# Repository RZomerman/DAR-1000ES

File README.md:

# Sony DAR-1000ES Conversion Project

This repository contains the project documentation converted from the original Word document into chapter-based GitHub Flavored Markdown.

## Chapters

For current AHCT wiring, brightness calculations and radio operation, start
with the [screen-driver operating guide](13-screen-driver-operating-guide.md).
Shared STB on **both** TD chips corrected the earlier multiplexing corruption;
clean 22-matrix text and scrolling were observed. Firmware 0.3.28 includes
internet radio, explicitly authorized full-width NOW PLAYING, and source
channel/bitrate/playback/genre indicators.
Installed 0.3.29 adds selectable Option 1 stereo spectrum (11 real PCM frequency
bands per channel), verified with isolated TD-model captures and decoded
stereo/mono/silence fixtures; the user confirmed the bars at 0.75% brightness.
Version 0.3.30 adds MONO 1/2 bank labels while retaining actual-source STEREO
and fixes measured scan gaps with longer DMA batching. A connected camera
snapshot confirms all 22 bars and STEREO/MONO 1/MONO 2/TUNED at 0.75%
per-grid duty. User confirmation of residual flicker is still pending;
a still image cannot establish temporal stability.
Physical voltage/current validation remains outstanding.
Firmware 0.3.31 boots with the fixed AHCT v2 GPIO map. Display output still
starts stopped; the legacy profile remains an isolated-only runtime option.
Installed firmware 0.3.32 adds eight display modes and shared short-/long-press
controls for a future Display Mode button, with 0.25% / 0.5% / 0.75% DIM cycling.
All eight modes and DIM cycling were checked on the isolated ESP; after
reconnection, Equalizer was restored at 0.75% per-grid duty.

For current display control, start with the
[fixed-element guide](08-esp-display-driver-specification.md#6-fixed-element-control-guide)
and [generic 5x7 matrix guide](08-esp-display-driver-specification.md#7-generic-5x7-matrix-guide).
The [annotated reference comparison](media/display-reference-coverage.svg)
matches every functional symbol in the FL701 drawing to an observed command.
Element mapping is complete at that level. Clean full-screen multiplexing
has now been observed with shared STB; electrical validation remains outstanding.

The [complete display bitmap catalogue](10-display-bitmap-catalogue.md)
includes 5x7 pixel patterns and HEX values for uppercase/lowercase letters,
digits, punctuation, a music note and seven level bars.

1. [DAR-1000ES Conversion](01-conversion.md)
2. [DAR-1000ES Display Control](02-display-control.md)
3. [DAR-1000ES Sound Path](03-sound-path.md)
4. [DAR-1000ES Program and Keypad Baseline](04-program-and-keypad-baseline.md)
5. [Bus Capture Findings and Key Reports](05-bus-capture-findings.md)
6. [Direct Display driving](06-direct-display-driving.md)
7. [Audio Control Findings and Next-Step Plan](07-audio-control-findings-and-plan.md)
8. [ESP32 Display-Driver Specification](08-esp-display-driver-specification.md)
9. [Music Note Bitmap](09-music-note-bitmap.md)
10. [Display Bitmap Catalogue](10-display-bitmap-catalogue.md)
11. [Live ESP32 Display Driver and Validation](11-live-display-driver-and-validation.md)
12. [TD62C950RF Timing Revalidation](12-td62c950rf-timing-revalidation.md)
13. [Screen Driver Operating Guide](13-screen-driver-operating-guide.md)
14. [Keypad Mapping](14-keypad-mapping.md)
15. [Split-setup Architecture and Travel Demo](15-split-setup-architecture.md)

Proposed behavior: [Chapter 18: Startup Procedure](18-startup-procedure.md)
specifies the snow/title sequence, saved station/brightness/display recovery and the
verification needed before automatic hardware-ready authorization can replace
manual confirmation. It is not implemented startup behavior.

Images used by the chapters are stored in [`media/`](media/).

The [ESP32 firmware](firmware/README-DAR-1000ES.md) includes internet radio,
the opt-in display timing/NOW PLAYING profile and the preserved upstream license.

## Control Integration Options

1. **Reuse the original controls (partially characterized):** Investigate the parallel bus between the system controller and display/front-panel controller IC701 before bypassing the original control firmware. See the [internal bus protocol specification](SONY_DAR1000ES_Protocol_Spec.md) and [2026-11-02 capture findings](05-bus-capture-findings.md). Passive captures establish repeatable framing and key/display correlations, but masked bits, driver ownership and electrical assumptions still block reliable emulation.
2. **Direct display-driver control (optically mapped, driver experimental):** Captures at IC702/IC703 establish a 26-slot scan, 40 segment clocks and one grid clock per slot. Controlled one-hot tests now map all 770 matrix dots and all fixed functional elements shown in the reference. See the [operating guide](13-screen-driver-operating-guide.md), [element guide](08-esp-display-driver-specification.md) and [capture/validation history](06-direct-display-driving.md). Shared STB on both TD chips now gives clean full-width text and scrolling; electrical margins and current remain unverified. [DAR-1000ES Display Control](02-display-control.md) retains the original hardware proposal, not current wiring instructions.

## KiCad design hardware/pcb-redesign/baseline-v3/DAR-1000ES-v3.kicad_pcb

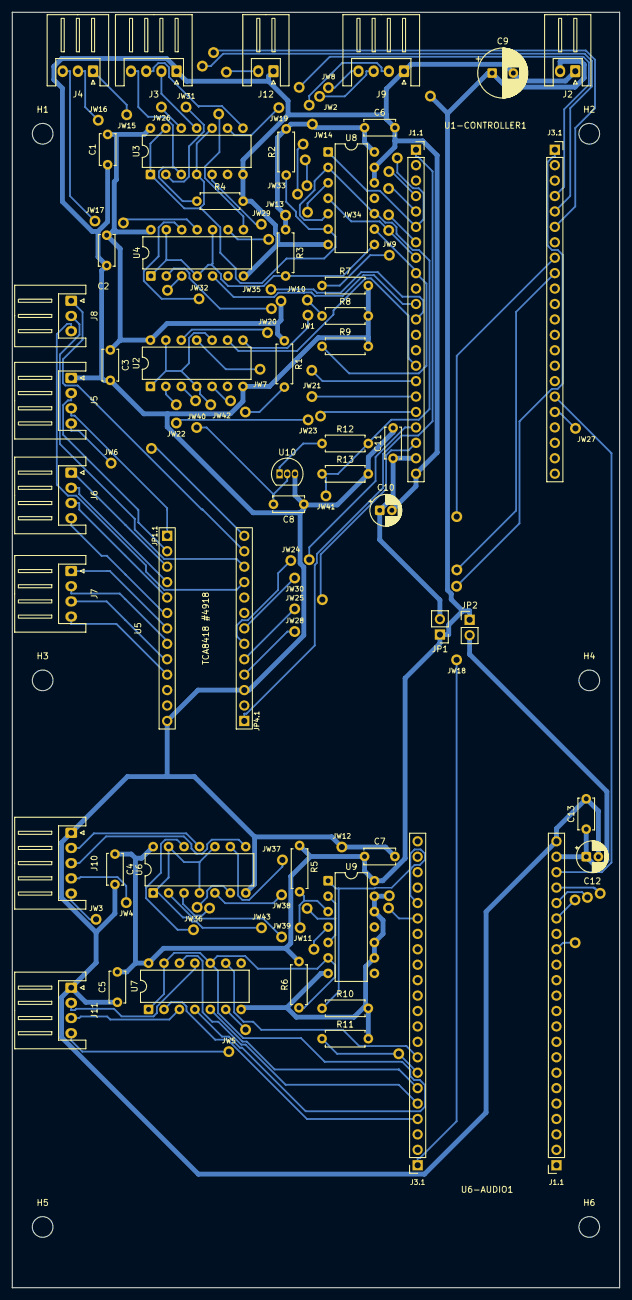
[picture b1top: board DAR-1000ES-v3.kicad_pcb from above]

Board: 2 copper layers, 100.0 x 210.0 mm, 99 parts (0 on the bottom side), 75 nets.

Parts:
C1, C2, C3, C4, C5: C; Bottom_Capacitor_THT__C_Disc_D5.0mm_W2.5mm_P5.00mm
C6, C7, C8, C11, C13: 100nF; Bottom_Capacitor_THT__C_Disc_D5.0mm_W2.5mm_P5.00mm
C9: 470uF 16V; Bottom_Capacitor_THT__CP_Radial_D8.0mm_P3.50mm
C10, C12: 100uF 16V; Bottom_Capacitor_THT__CP_Radial_D5.0mm_P2.00mm
H1, H2, H3, H4, H5, H6: M3_Clearance_3.4mm; MountingHole_3.4mm_M3_NPTH
J2: Conn_01x02; Bottom_Connector_JST__JST_XH_S2B-XH-A_1x02_P2.50mm_Horizont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
J3, J5, J6, J7, J9, J11: Conn_01x04; Bottom_Connector_JST__JST_XH_S4B-XH-A_1x04_P2.50mm_Horizont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
J4, J8: Conn_01x03; Bottom_Connector_JST__JST_XH_S3B-XH-A_1x03_P2.50mm_Horizont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
J10: DAC CONTROL; Bottom_Connector_JST__JST_XH_S5B-XH-A_1x05_P2.50mm_Horizont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
J12: SONY_5V_SENSE; Bottom_Connector_JST__JST_XH_S2B-XH-A_1x02_P2.50mm_Horizont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
JP1, JP2: Jumper_2_Bridged; Bottom_Connector_PinHeader_2.54mm__PinHeader_1x02_P2.54mm_V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
JW1: Insulated wire link; Bottom_InsulatedWire_JW1
JW2: Insulated wire link; Bottom_InsulatedWire_JW2
JW3: Insulated wire link; Bottom_InsulatedWire_JW3
JW4: Insulated wire link; Bottom_InsulatedWire_JW4
JW5: Insulated wire link; Bottom_InsulatedWire_JW5
JW6: Insulated wire link; Bottom_InsulatedWire_JW6
JW7: Insulated wire link; Bottom_InsulatedWire_JW7
JW8: Insulated wire link; Bottom_InsulatedWire_JW8
JW9: Insulated wire link; Bottom_InsulatedWire_JW9
JW10: Insulated wire link; Bottom_InsulatedWire_JW10
JW11: Insulated wire link; Bottom_InsulatedWire_JW11
JW12: Insulated wire link; Bottom_InsulatedWire_JW12
JW13: Insulated wire link; Bottom_InsulatedWire_JW13
JW14: Insulated wire link; Bottom_InsulatedWire_JW14
JW15: Insulated wire link; Bottom_InsulatedWire_JW15
JW16: Insulated wire link; Bottom_InsulatedWire_JW16
JW17: Insulated wire link; Bottom_InsulatedWire_JW17
JW18: Insulated wire link; Bottom_InsulatedWire_JW18
JW19: Insulated wire link; Bottom_InsulatedWire_JW19
JW20: Insulated wire link; Bottom_InsulatedWire_JW20
JW21: Insulated wire link; Bottom_InsulatedWire_JW21
JW22: Insulated wire link; Bottom_InsulatedWire_JW22
JW23: Insulated wire link; Bottom_InsulatedWire_JW23
JW24: Insulated wire link; Bottom_InsulatedWire_JW24
JW25: Insulated wire link; Bottom_InsulatedWire_JW25
JW26: Insulated wire link; Bottom_InsulatedWire_JW26
JW27: Insulated wire link; Bottom_InsulatedWire_JW27
JW28: Insulated wire link; Bottom_InsulatedWire_JW28
JW29: Insulated wire link; Bottom_InsulatedWire_JW29
JW30: Insulated wire link; Bottom_InsulatedWire_JW30
JW31: Insulated wire link; Bottom_InsulatedWire_JW31
JW32: Insulated wire link; Bottom_InsulatedWire_JW32
JW33: Insulated wire link; Bottom_InsulatedWire_JW33
JW34: Insulated wire link; Bottom_InsulatedWire_JW34
JW35: Insulated wire link; Bottom_InsulatedWire_JW35
JW36: Insulated wire link; Bottom_InsulatedWire_JW36
JW37: Insulated wire link; Bottom_InsulatedWire_JW37
JW38: Insulated wire link; Bottom_InsulatedWire_JW38
JW39: Insulated wire link; Bottom_InsulatedWire_JW39
JW40: Insulated wire link; Bottom_InsulatedWire_JW40
JW41: Insulated wire link; Bottom_InsulatedWire_JW41
JW42: Insulated wire link; Bottom_InsulatedWire_JW42
JW43: Insulated wire link; Bottom_InsulatedWire_JW43
R1, R2, R3, R4, R5, R6: 10k; Bottom_Resistor_THT__R_Axial_DIN0207_L6.3mm_D2.5mm_P7.62mm_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
R7, R8, R9, R10, R11, R13: 100k; Bottom_Resistor_THT__R_Axial_DIN0207_L6.3mm_D2.5mm_P7.62mm_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
R12: 1k; Bottom_Resistor_THT__R_Axial_DIN0207_L6.3mm_D2.5mm_P7.62mm_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
U1-CONTROLLER1, U6-AUDIO1: ESP32-S3-DevKitC-1-N16R8; Bottom_DAR1000ES__ESP32-S3-DevKitC-1_2xSocket_1x22_P2.54mm_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
U2, U3, U4, U6, U7: SN74AHCT125N; Bottom_Package_DIP__DIP-14_W7.62mm
U5: Adafruit_TCA8418_4918; Bottom_DAR1000ES__Adafruit_TCA8418_4918_2x13_P2.54mm_W12.70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
U8, U9: SN74AHCT00N; Bottom_Package_DIP__DIP-14_W7.62mm
U10: MCP100-475DI/TO; Bottom_Package_TO_SOT_THT__TO-92_Inline

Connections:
/A.MUTE: J9.2, JW1.1, U2.8
/ATT: J10.2, U6.11
/BCKI: J11.2, U7.11
/D.MUTE: J9.3, JW2.1, U2.3
/DATA: J11.3, U7.3
/FLCLEAR: J3.4, R4.1, U3.3
/FLGCLK: J3.3, U3.8
/FLGDATA: J3.2, U3.11
/IN0: J6.1, U5.JP1.3 (C0)
/IN1: J6.2, U5.JP1.4 (C1)
/IN2: J6.3, U5.JP1.5 (C2)
/IN3: J6.4, U5.JP1.6 (C3)
/IN4: J7.1, U5.JP1.7 (C4)
/IN5: J7.2, U5.JP1.8 (C5)
/IN6: J7.3, U5.JP1.9 (C6)
/IN7: J7.4, U5.JP1.10 (C7)
/INIT: J10.5, JW3.1, U6.3
/LATCH: J10.4, JW4.1, U6.6
/LRCK: J11.4, JW5.1, U7.6
/OUT0: J5.2, U5.JP1.2 (R0)
/OUT1: J5.3, U5.JP1.1 (R1)
/OUT2: J5.4, JW6.1, U5.JP4.13 (R2)
/OUT3: J8.1, U5.JP4.12 (R3)
/OUT4: J8.2, U5.JP4.11 (R4)
/OUT5: J8.3, U5.JP4.10 (R5)
/RELAY: J9.4, JW7.1, JW8.1, U2.11
/SHIFT: J10.3, U6.8
ENABLE_U2: JW9.1, R7.1, U1-CONTROLLER1.J1.6 (IO6), U8.1 (1A)
ENABLE_U3: JW10.1, R8.1, U1-CONTROLLER1.J1.8 (IO15), U8.4 (2A)
ENABLE_U4: R9.1, U1-CONTROLLER1.J1.9 (IO16), U8.9 (3A)
ENABLE_U6: R10.1, U6-AUDIO1.J3.18 (IO21), U9.1 (1A)
ENABLE_U7: JW11.1, R11.1, U6-AUDIO1.J3.7 (IO41), U9.4 (2A)
ESP_AUDIO_5V: C12.1, C13.1, JP2.2 (B), U6-AUDIO1.J1.21 (5V)
ESP_CTRL_5V: C10.1, C11.1, JP1.2 (B), U1-CONTROLLER1.J1.21 (5V)
GND: C1.1, C2.1, C3.2, C4.2, C5.1, C6.2, C7.2, C8.2, C9.2, C10.2, C11.2, C12.2, C13.2, J2.1, J3.1, J5.1, J9.1, J10.1, J11.1, J12.1, JW12.1, R4.2, R7.2, R8.2, R9.2, R10.2, R11.2, R13.2, U1-CONTROLLER1.J1.22 (GND), U2.7 (GND), U3.7 (GND), U4.7 (GND), U5.JP1.13 (GND), U5.JP4.3 (GND), U6.7 (GND), U6-AUDIO1.J1.22 (GND), U7.7 (GND), U8.7 (GND), U8.12 (4A), U8.13 (4B), U9.7 (GND), U9.9 (3A), U9.10 (3B), U9.12 (4A), U9.13 (4B), U10.3 (GND)
LOCAL_5V: C1.2, C2.2, C3.1, C4.1, C5.2, C6.1, C7.1, C9.1, J2.2, JP1.1 (A), JP2.1 (A), JW13.1, JW14.1, R1.1, R2.2, R3.1, R5.1, R6.2, U2.14 (VCC), U3.14 (VCC), U4.14 (VCC), U6.14 (VCC), U7.14 (VCC), U8.14 (VCC), U9.14 (VCC)
unnamed: J4.1, JW15.1, U4.8
unnamed: J4.2, JW16.1, U4.3
unnamed: J4.3, JW17.1, U4.11
unnamed: JW18.1, U1-CONTROLLER1.J3.1 (GND), U6-AUDIO1.J3.1 (GND)
unnamed: JW19.1, U1-CONTROLLER1.J3.4 (IO1), U3.9
unnamed: JW26.1, U1-CONTROLLER1.J3.5 (IO2), U3.12
unnamed: JW29.1, U1-CONTROLLER1.J1.4 (IO4), U3.5
unnamed: JW32.1, JW33.1, U1-CONTROLLER1.J1.5 (IO5), U4.12
unnamed: JW34.1, U1-CONTROLLER1.J1.7 (IO7), U4.9
unnamed: JW35.1, U1-CONTROLLER1.J1.12 (IO8), U4.2
unnamed: U1-CONTROLLER1.J1.15 (IO9), U2.9
unnamed: JW20.1, U1-CONTROLLER1.J1.16 (IO10), U2.12
unnamed: JW21.1, U1-CONTROLLER1.J1.17 (IO11), U2.5
unnamed: JW22.1, JW23.1, U1-CONTROLLER1.J1.18 (IO12), U2.2
unnamed: JW24.1, U1-CONTROLLER1.J1.19 (IO13), U5.JP4.6 (~INT)
unnamed: JW25.1, U1-CONTROLLER1.J1.20 (IO14), U5.JP4.5 (SDA)
unnamed: U1-CONTROLLER1.J1.11 (IO18), U4.5
unnamed: JW27.1, U1-CONTROLLER1.J3.18 (IO21), U6-AUDIO1.J1.19 (IO13)
unnamed: JW28.1, U1-CONTROLLER1.J3.9 (IO39), U5.JP4.4 (SCL)
unnamed: JW30.1, U1-CONTROLLER1.J3.8 (IO40), U5.JP4.7 (~RST)
unnamed: JW31.1, U1-CONTROLLER1.J3.6 (IO42), U3.2
unnamed: U1-CONTROLLER1.J3.17 (IO47), U6-AUDIO1.J1.20 (IO14)
unnamed: U1-CONTROLLER1.J1.1 (3V3), U5.JP4.1 (VIN)
unnamed: U6-AUDIO1.J3.4 (IO1), U7.2
unnamed: U6-AUDIO1.J3.5 (IO2), U7.12
unnamed: JW39.1, U6.2, U6-AUDIO1.J1.15 (IO9)
unnamed: JW36.1, U6.12, U6-AUDIO1.J1.17 (IO11)
unnamed: JW37.1, U6.9, U6-AUDIO1.J1.18 (IO12)
unnamed: U6-AUDIO1.J3.8 (IO40), U7.9
unnamed: U6-AUDIO1.J3.6 (IO42), U7.5
unnamed: JW38.1, U6.5, U6-AUDIO1.J3.17 (IO47)
SONY_5V_SENSE: C8.1, J12.2, JW40.1, U10.2 (VDD_SONY)
SONY_POWER_GOOD: JW41.1, R12.2, R13.1, U8.2 (1B), U8.5 (2B), U8.10 (3B), U9.2 (1B), U9.5 (2B)
SONY_RESET_N_RAW: R12.1, U10.1 (~RESET)
U2_OE_N: JW42.1, R1.2, U2.1, U2.4, U2.10, U2.13, U8.3 (1Y)
U3_OE_N: R2.1, U3.1, U3.4, U3.10, U3.13, U8.6 (2Y)
U4_OE_N: R3.2, U4.1, U4.4, U4.10, U4.13, U8.8 (3Y)
U6_OE_N: JW43.1, R5.2, U6.1, U6.4, U6.10, U6.13, U9.3 (1Y)
U7_OE_N: R6.1, U7.1, U7.4, U7.10, U7.13, U9.6 (2Y)

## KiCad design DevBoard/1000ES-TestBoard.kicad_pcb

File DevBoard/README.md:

# Sony DAR-1000ES ESP32 Development Board

## Overview

**Design proposal, not a hardware-validation report.** This document describes
the intended three-ESP development board, not the pinout of the current
display-test harness. The [current display-control guide](../08-esp-display-driver-specification.md)
records confirmed element mapping; it does not establish that this board's
audio, bus, keypad, power or isolation features have been validated.

This development board is designed as the primary hardware platform for the **Sony DAR-1000ES modernization project**. It enables rapid experimentation with multiple integration strategies while preserving the original Sony hardware wherever possible.

The board incorporates **three ESP32-S3 controllers**, although only two are expected to be required for the final solution. The third controller is included specifically as a contingency path for direct display control if communication through the original Sony system controller (IC701) proves impractical.

The objective of this board is to validate all critical hardware interfaces before committing to a final production design.

---

## Design Goals

The board supports testing of four major functional areas:

### 1. Digital Audio Injection

A dedicated Audio ESP is responsible for generating digital audio and feeding it directly into the Sony audio processing chain.

Target interface:

| Signal | Destination |
|----------|----------|
| ATT/SHIFT/LATCH | IC501 |
| LRCKI | IC501 |
| DATAI | IC501 |
| BCKI | IC501 |

This allows the DAR-1000ES to receive modern digital audio streams while continuing to use the original Sony DAC and audio circuitry.

---

### 2. IC701 Controller Bus Injection

The primary Controller ESP is intended to test emulation and injection on the internal Sony communication bus. **This has not been validated.** This is **Option 1**: investigate retaining IC701, the display/front-panel controller, and the default controls before directly driving IC702 and IC703.

See the [unvalidated internal bus protocol proposal](../SONY_DAR1000ES_Protocol_Spec.md) for the working hypotheses and required validation. Signal directions, timing, electrical assumptions, and message formats are not established.

Supported signals:

| Signal |
|----------|
| DBS0-DBS7 |
| ACK |
| STB |
| REQ |
| NCK |

The intention is to determine whether the original firmware architecture can be leveraged by communicating with IC701 over its interface to the system controller.

If successful, this becomes the preferred approach because it preserves most of the original Sony subsystem interactions.

---

### 2b. Direct Sony Hardware Control

In addition to bus injection, the Controller ESP can directly control critical DAR-1000ES hardware signals.

Supported outputs include:

| Function |
|----------|
| D.MUTE |
| A.MUTE |
| Audio Relay |
| Power Control |
| Reset Control |

These are intended control outputs, not established safe drive procedures.
Verify their actual voltage, polarity, ownership and reset behavior before
using them, even if communication through the original controller fails.

---

### 2c. Keypad Matrix Interface

The board provides direct access to the original Sony button matrix.

Capabilities:

- Scan front-panel buttons
- Decode keypad presses
- Replace original controller functionality
- Support future custom user interface options

The proposed keypad interface uses a dedicated keypad controller. Isolate
IC701 from all fourteen matrix nets before enabling another scanner;
reliable operation and physical key positions still need validation.
See the [keypad design baseline](../04-program-and-keypad-baseline.md).

---

### 3. Direct Display Driver Control (Fallback Strategy)

A third ESP32-S3 is included exclusively as a backup solution.

If direct IC701 bus injection does not provide sufficient control of the front-panel display, this ESP can take over the display subsystem directly.

Target functionality includes:

- Direct control of display driver ICs
- Row driving
- Column driving
- Segment updates
- Custom display rendering

This completely bypasses the original display control architecture and provides maximum flexibility for future software development.

---

## Controller Architecture

### Audio ESP

Primary responsibility:

- Streaming audio reception
- Audio decoding
- I²S generation
- Interface to IC501

Interfaces:

- Audio output signals
- UART communication with Controller ESP

---

### Controller ESP

Primary responsibility:

- System orchestration
- IC701 bus injection
- Sony hardware control
- Keypad processing

Interfaces:

- Bus emulation
- Control outputs
- Keypad matrix
- UART communication

---

### Display ESP

Primary responsibility:

- Display subsystem experimentation
- Direct display driver control
- Fallback display architecture

Interfaces:

- Row control
- Column control
- UART communication

---

## ESP-to-ESP Communication

The three ESP32 controllers can communicate through dedicated UART links.

This architecture allows:

- Separation of audio processing from system control
- Reduced software complexity
- Independent firmware development
- Easier debugging and validation

The Audio ESP and Display ESP act as peripherals while the Controller ESP functions as the primary coordinator.

---

## Power Architecture

Although each ESP controller has its own USB-C connector, USB is intended primarily for:

- Firmware upload
- Debugging
- Serial console access

Normal operating power is supplied directly from the Sony DAR-1000ES.

Features include:

- Independent ESP enable/disable jumpers
- Selective controller isolation
- Simplified troubleshooting
- Reduced power consumption during testing

This allows any controller to be disabled while maintaining operation of the remaining subsystems.

Disabling a controller or its power jumper does not by itself establish
electrical isolation of its signal pins. Verify buffer enables, power-state
behavior and original-controller ownership; do not assume an unpowered ESP
or Sony input is safe to back-drive.

---

## PCB Design Philosophy

To minimize manufacturing cost and simplify assembly, the PCB has been intentionally designed as a:

**Single-layer board**

Characteristics:

- Single copper layer
- Limited number of wire bridges
- Large ground areas
- Easy inspection and rework
- Low fabrication cost

The use of a mostly single-sided layout also makes future modifications straightforward during the experimental phase of the project.

---

## Development Strategy

The board is intended to validate three possible integration levels:

### Level 1 – Audio Only

- Audio ESP operational
- Original Sony control system retained

### Level 2 – IC701 Emulation

- Controller ESP injects Sony bus traffic
- Original display drivers retained
- Original Sony architecture largely preserved

### Level 3 – Full Replacement

- Controller ESP replaces IC701 functionality
- Display ESP directly drives display hardware
- Complete modern control stack running on ESP32 controllers

---

## Current Status

This development-board design is a proposed validation platform for the
DAR-1000ES retrofit effort, not proof of a tested complete hardware platform.

The modular three-ESP architecture provides multiple fallback paths, ensuring that all major subsystems can be independently evaluated before a final production design is selected.

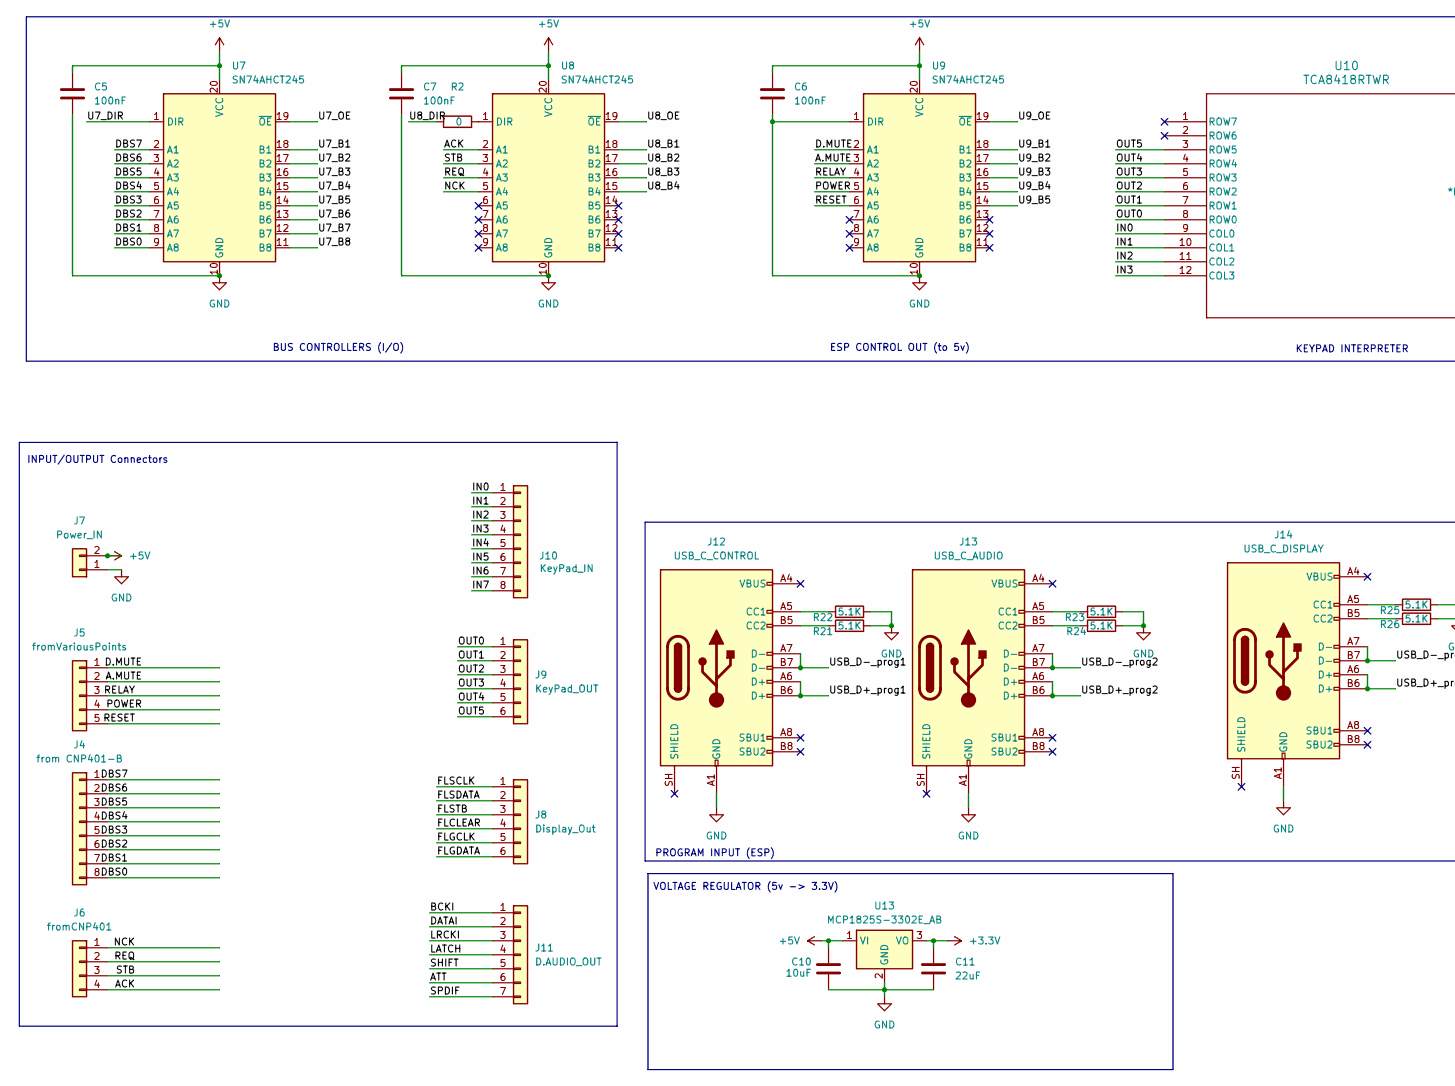
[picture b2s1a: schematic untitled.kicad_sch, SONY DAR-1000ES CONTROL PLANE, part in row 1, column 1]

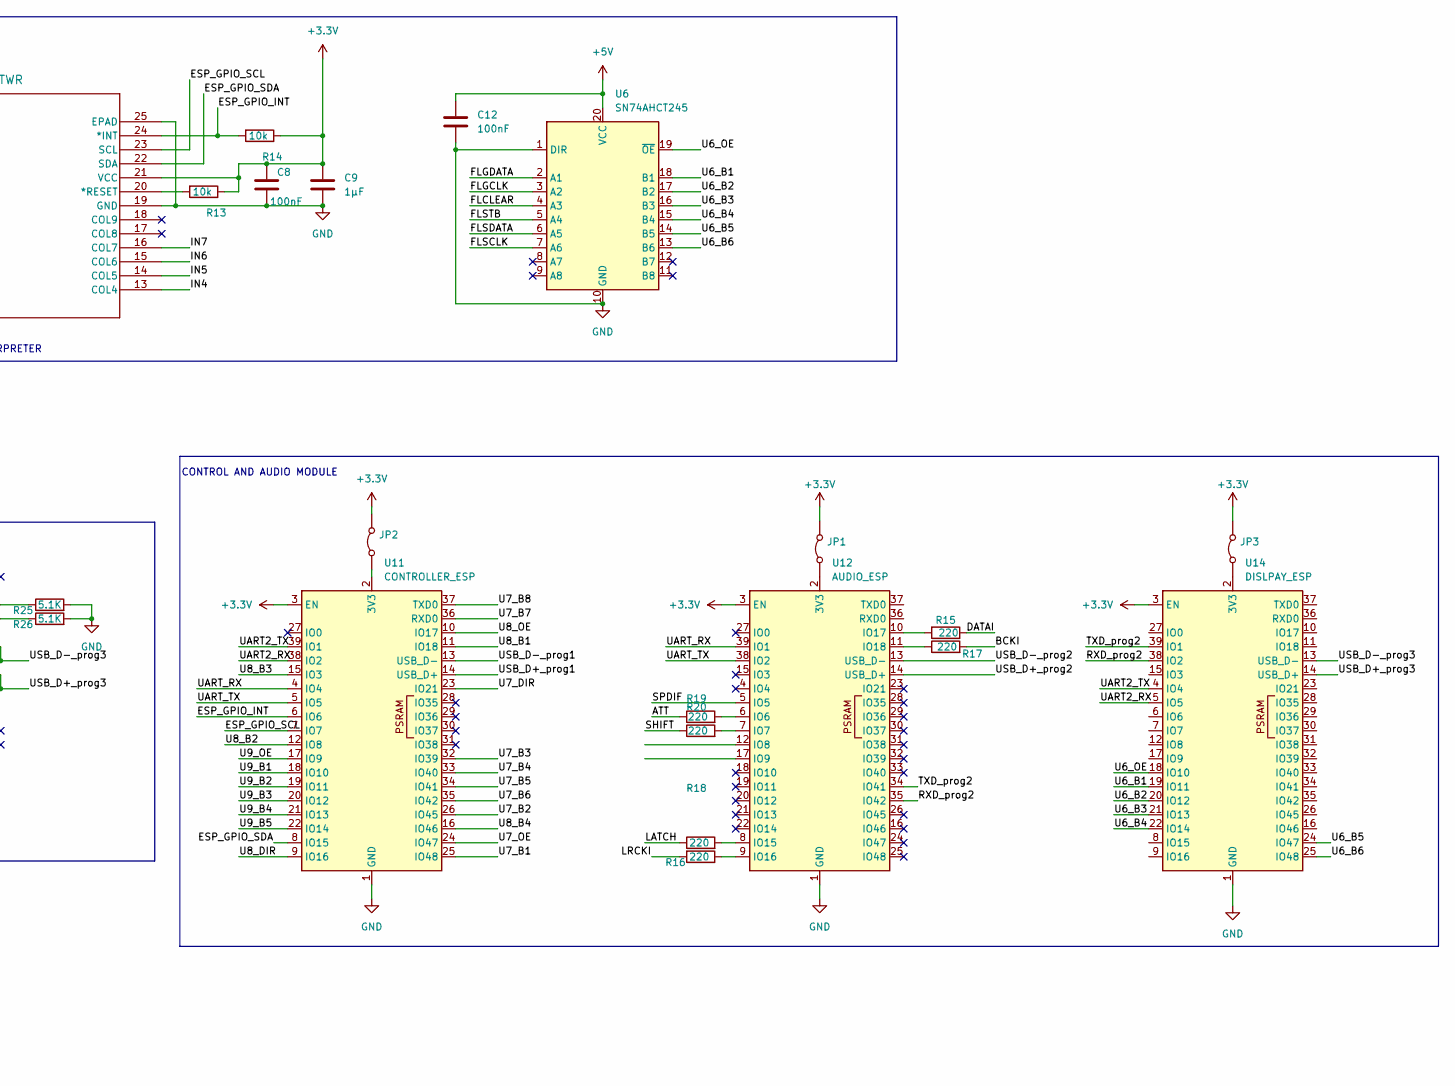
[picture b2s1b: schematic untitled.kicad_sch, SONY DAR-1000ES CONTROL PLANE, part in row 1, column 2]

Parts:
C5, C6, C7, C8, C12: 100nF; C_Elec_4x5.4
C9: 1µF; C_Elec_4x5.4
C10: 10uF; C_Elec_4x5.4
C11: 22uF; C_Elec_4x5.4
J4: from CNP401-B; JST_PH_B8B-PH-K_1x08_P2.00mm_Vertical
J5: fromVariousPoints; JST_PH_B5B-PH-K_1x05_P2.00mm_Vertical
J6: fromCNP401; JST_PH_B4B-PH-K_1x04_P2.00mm_Vertical
J7: Power_IN; JST_PH_B2B-PH-K_1x02_P2.00mm_Vertical
J8: Display_Out; JST_PH_B8B-PH-K_1x08_P2.00mm_Vertical
J9: KeyPad_OUT; JST_PH_B6B-PH-K_1x06_P2.00mm_Vertical
J10: KeyPad_IN; JST_PH_B8B-PH-K_1x08_P2.00mm_Vertical
J11: D.AUDIO_OUT; JST_PH_B7B-PH-K_1x07_P2.00mm_Vertical
J12: USB_C_CONTROL; USB_C_Receptacle_GCT_USB4105-xx-A_16P_TopMnt_Horizontal
J13: USB_C_AUDIO; USB_C_Receptacle_GCT_USB4105-xx-A_16P_TopMnt_Horizontal
J14: USB_C_DISPLAY; USB_C_Receptacle_GCT_USB4105-xx-A_16P_TopMnt_Horizontal
JP1, JP2, JP3: Jumper_2_Bridged; SolderJumper-2_P1.3mm_Bridged2Bar_Pad1.0x1.5mm
R2: 0; R_Axial_DIN0204_L3.6mm_D1.6mm_P5.08mm_Horizontal
R13, R14: 10k; R_0508_1220Metric_Pad1.12x2.15mm_HandSolder
R15, R16, R17, R18, R19, R20: 220; R_0508_1220Metric_Pad1.12x2.15mm_HandSolder
R21, R22, R23, R24, R25, R26: 5.1K; R_0508_1220Metric_Pad1.12x2.15mm_HandSolder
U6, U7, U8, U9: SN74AHCT245; TSSOP-20_4.4x6.5mm_P0.65mm
U10: TCA8418RTWR; QFN-24-1EP_4x4mm_P0.5mm_EP2.7x2.7mm
U11: CONTROLLER_ESP; ESP32-S3-WROOM-1
U12: AUDIO_ESP; ESP32-S3-WROOM-1
U13: MCP1825S-3302E_AB; TO-220-3_Vertical
U14: DISLPAY_ESP; ESP32-S3-WROOM-1

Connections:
+3.3V: C8.1, C9.1, C11.1, JP1.2 (B), JP2.2 (B), JP3.2 (B), R13.1, R14.1, U10.21 (VCC), U11.3 (EN), U12.3 (EN), U13.3 (VO), U14.3 (EN); also elsewhere on the board
+5V: C5.1, C6.1, C7.1, C10.1, C12.1, J7.2, U6.20 (VCC), U7.20 (VCC), U8.20 (VCC), U9.20 (VCC), U13.1 (VI)
/ES1000-Default/A.MUTE: J5.2, U9.3 (A2)
/ES1000-Default/ACK: J6.4, U8.2 (A1)
/ES1000-Default/ATT: J11.6, R20.1
/ES1000-Default/BCKI: J11.1, R17.2
/ES1000-Default/D.MUTE: J5.1, U9.2 (A1)
/ES1000-Default/DATAI: J11.2, R15.1
/ES1000-Default/DBS0: J4.8, U7.9 (A8)
/ES1000-Default/DBS1: J4.7, U7.8 (A7)
/ES1000-Default/DBS2: J4.6, U7.7 (A6)
/ES1000-Default/DBS3: J4.5, U7.6 (A5)
/ES1000-Default/DBS4: J4.4, U7.5 (A4)
/ES1000-Default/DBS5: J4.3, U7.4 (A3)
/ES1000-Default/DBS6: J4.2, U7.3 (A2)
/ES1000-Default/DBS7: J4.1, U7.2 (A1)
/ES1000-Default/ESP_GPIO_INT: R14.2, U10.24 (*INT), U11.6 (IO6)
/ES1000-Default/ESP_GPIO_SCL: U10.23 (SCL), U11.7 (IO7)
/ES1000-Default/ESP_GPIO_SDA: U10.22 (SDA), U11.8 (IO15)
/ES1000-Default/FLCLEAR: J8.4, U6.4 (A3)
/ES1000-Default/FLGCLK: J8.5, U6.3 (A2)
/ES1000-Default/FLGDATA: J8.6, U6.2 (A1)
/ES1000-Default/FLSCLK: J8.1, U6.7 (A6)
/ES1000-Default/FLSDATA: J8.2, U6.6 (A5)
/ES1000-Default/FLSTB: J8.3, U6.5 (A4)
/ES1000-Default/IN0: J10.1, U10.9 (COL0)
/ES1000-Default/IN1: J10.2, U10.10 (COL1)
/ES1000-Default/IN2: J10.3, U10.11 (COL2)
/ES1000-Default/IN3: J10.4, U10.12 (COL3)
/ES1000-Default/IN4: J10.5, U10.13 (COL4)
/ES1000-Default/IN5: J10.6, U10.14 (COL5)
/ES1000-Default/IN6: J10.7, U10.15 (COL6)
/ES1000-Default/IN7: J10.8, U10.16 (COL7)
/ES1000-Default/LATCH: J11.4, R18.1
/ES1000-Default/LRCKI: J11.3, R16.2
/ES1000-Default/NCK: J6.1, U8.5 (A4)
/ES1000-Default/OUT0: J9.1, U10.8 (ROW0)
/ES1000-Default/OUT1: J9.2, U10.7 (ROW1)
/ES1000-Default/OUT2: J9.3, U10.6 (ROW2)
/ES1000-Default/OUT3: J9.4, U10.5 (ROW3)
/ES1000-Default/OUT4: J9.5, U10.4 (ROW4)
/ES1000-Default/OUT5: J9.6, U10.3 (ROW5)
/ES1000-Default/POWER: J5.4, U9.5 (A4)
/ES1000-Default/RELAY: J5.3, U9.4 (A3)
/ES1000-Default/REQ: J6.2, U8.4 (A3)
/ES1000-Default/RESET: J5.5, U9.6 (A5)
/ES1000-Default/RXD_prog2: U12.35 (IO42), U14.38 (IO2)
/ES1000-Default/SHIFT: J11.5, R19.1
/ES1000-Default/SPDIF: J11.7, U12.5 (IO5)
/ES1000-Default/STB: J6.3, U8.3 (A2)
/ES1000-Default/TXD_prog2: U12.34 (IO41), U14.39 (IO1)
/ES1000-Default/U6_B1: U6.18 (B1), U14.19 (IO11)
/ES1000-Default/U6_B2: U6.17 (B2), U14.20 (IO12)
/ES1000-Default/U6_B3: U6.16 (B3), U14.21 (IO13)
/ES1000-Default/U6_B4: U6.15 (B4), U14.22 (IO14)
/ES1000-Default/U6_B5: U6.14 (B5), U14.24 (IO47)
/ES1000-Default/U6_B6: U6.13 (B6), U14.25 (IO48)
/ES1000-Default/U6_OE: U6.19 (~OE), U14.18 (IO10)
/ES1000-Default/U7_B1: U7.18 (B1), U11.25 (IO48)
/ES1000-Default/U7_B2: U7.17 (B2), U11.26 (IO45)
/ES1000-Default/U7_B3: U7.16 (B3), U11.32 (IO39)
/ES1000-Default/U7_B4: U7.15 (B4), U11.33 (IO40)
/ES1000-Default/U7_B5: U7.14 (B5), U11.34 (IO41)
/ES1000-Default/U7_B6: U7.13 (B6), U11.35 (IO42)
/ES1000-Default/U7_B7: U7.12 (B7), U11.36 (RXD0)
/ES1000-Default/U7_B8: U7.11 (B8), U11.37 (TXD0)
/ES1000-Default/U7_DIR: U7.1 (DIR), U11.23 (IO21)
/ES1000-Default/U7_OE: U7.19 (~OE), U11.24 (IO47)
/ES1000-Default/U8_B1: U8.18 (B1), U11.11 (IO18)
/ES1000-Default/U8_B2: U8.17 (B2), U11.12 (IO8)
/ES1000-Default/U8_B3: U8.16 (B3), U11.15 (IO3)
/ES1000-Default/U8_B4: U8.15 (B4), U11.16 (IO46)
/ES1000-Default/U8_DIR: R2.1, U11.9 (IO16)
/ES1000-Default/U8_OE: U8.19 (~OE), U11.10 (IO17)
/ES1000-Default/U9_B1: U9.18 (B1), U11.18 (IO10)
/ES1000-Default/U9_B2: U9.17 (B2), U11.19 (IO11)
/ES1000-Default/U9_B3: U9.16 (B3), U11.20 (IO12)
/ES1000-Default/U9_B4: U9.15 (B4), U11.21 (IO13)
/ES1000-Default/U9_B5: U9.14 (B5), U11.22 (IO14)
/ES1000-Default/U9_OE: U9.19 (~OE), U11.17 (IO9)
/ES1000-Default/UART2_RX: U11.38 (IO2), U14.5 (IO5)
/ES1000-Default/UART2_TX: U11.39 (IO1), U14.4 (IO4)
/ES1000-Default/UART_RX: U11.4 (IO4), U12.39 (IO1)
/ES1000-Default/UART_TX: U11.5 (IO5), U12.38 (IO2)
/ES1000-Default/USB_D+_prog1: J12.A6 (D+), J12.B6 (D+), U11.14 (USB_D+)
/ES1000-Default/USB_D+_prog2: J13.A6 (D+), J13.B6 (D+), U12.14 (USB_D+)
/ES1000-Default/USB_D+_prog3: J14.A6 (D+), J14.B6 (D+), U14.14 (USB_D+)
/ES1000-Default/USB_D-_prog1: J12.A7 (D-), J12.B7 (D-), U11.13 (USB_D-)
/ES1000-Default/USB_D-_prog2: J13.A7 (D-), J13.B7 (D-), U12.13 (USB_D-)
/ES1000-Default/USB_D-_prog3: J14.A7 (D-), J14.B7 (D-), U14.13 (USB_D-)
GND: C5.2, C6.2, C7.2, C8.2, C9.2, C10.2, C11.2, C12.2, J7.1, J8.8, J12.A1 (GND), J12.A12 (GND), J12.B1 (GND), J12.B12 (GND), J13.A1 (GND), J13.A12 (GND), J13.B1 (GND), J13.B12 (GND), J14.A1 (GND), J14.A12 (GND), J14.B1 (GND), J14.B12 (GND), R21.2, R22.2, R23.2, R24.2, R25.2, R26.2, U6.1 (DIR), U6.10 (GND), U7.10 (GND), U8.10 (GND), U9.1 (DIR), U9.10 (GND), U10.19 (GND), U10.25 (EPAD), U11.1 (GND), U11.40 (GND), U11.41 (GND), U12.1 (GND), U12.40 (GND), U12.41 (GND), U13.2 (GND), U14.1 (GND), U14.40 (GND), U14.41 (GND)
unnamed: J12.A5 (CC1), R22.1
unnamed: J12.B5 (CC2), R21.1
unnamed: J13.A5 (CC1), R23.1
unnamed: J13.B5 (CC2), R24.1
unnamed: J14.A5 (CC1), R25.1
unnamed: J14.B5 (CC2), R26.1
unnamed: JP1.1 (A), U12.2 (3V3)
unnamed: JP2.1 (A), U11.2 (3V3)
unnamed: JP3.1 (A), U14.2 (3V3)
unnamed: R2.2, U8.1 (DIR)
unnamed: R13.2, U10.20 (*RESET)
unnamed: R20.2, U12.6 (IO6)
unnamed: R19.2, U12.7 (IO7)
unnamed: R18.2, U12.8 (IO15)
unnamed: R16.1, U12.9 (IO16)
unnamed: R15.2, U12.10 (IO17)
unnamed: R17.1, U12.11 (IO18)

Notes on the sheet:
BUS CONTROLLERS (I/O)
VOLTAGE REGULATOR (5v -> 3.3V)
ESP CONTROL OUT (to 5v)
KEYPAD INTERPRETER
INPUT/OUTPUT Connectors
PROGRAM INPUT (ESP)
CONTROL AND AUDIO MODULE

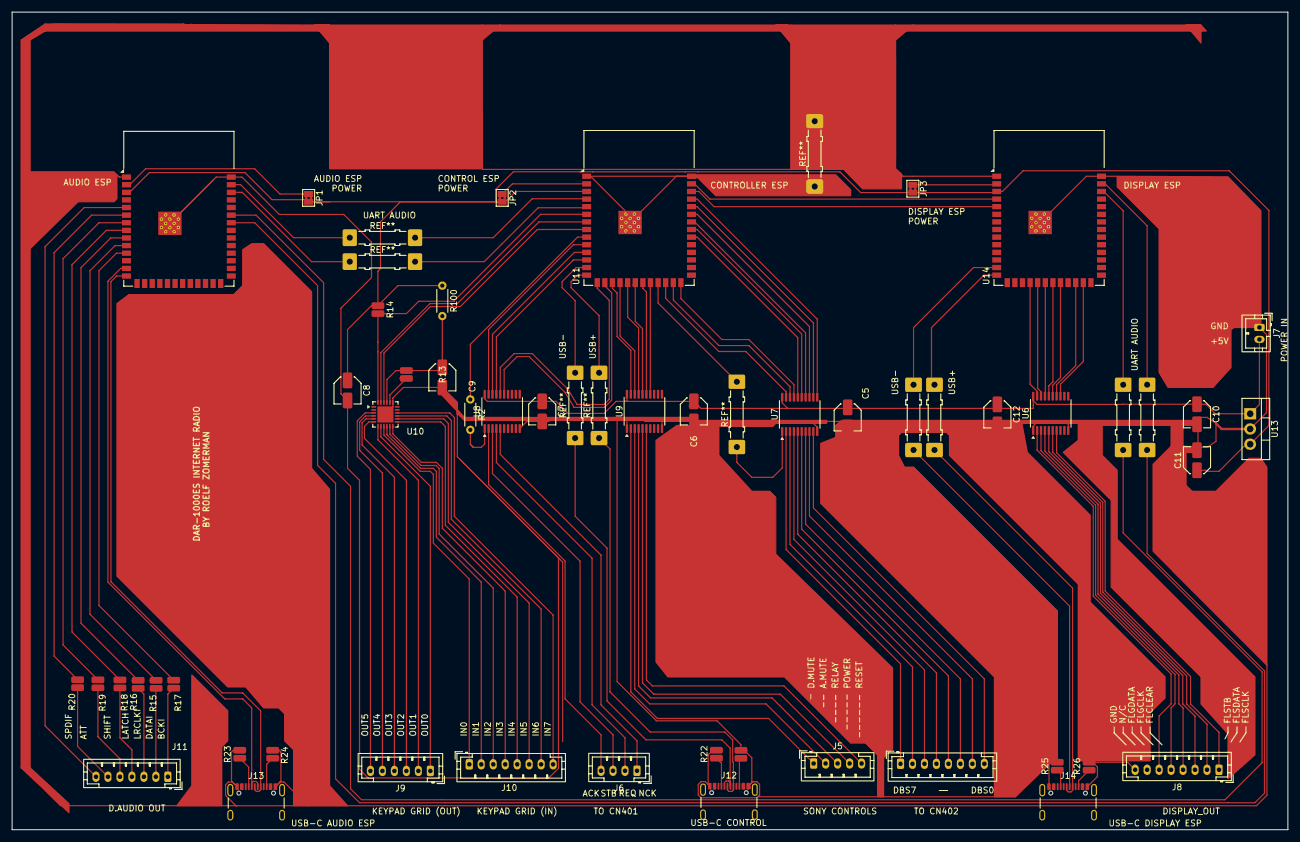
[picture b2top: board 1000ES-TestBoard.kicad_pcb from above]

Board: 2 copper layers, 213.0 x 136.5 mm, 47 parts (0 on the bottom side), 108 nets.

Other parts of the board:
R100: 0; R_Axial_DIN0204_L3.6mm_D1.6mm_P5.08mm_Horizontal

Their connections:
+3.3V: R100.1, R100.2; also elsewhere on the board
